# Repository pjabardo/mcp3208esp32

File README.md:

# mcp3208esp32
MCP3208 data acquisition with ESP32

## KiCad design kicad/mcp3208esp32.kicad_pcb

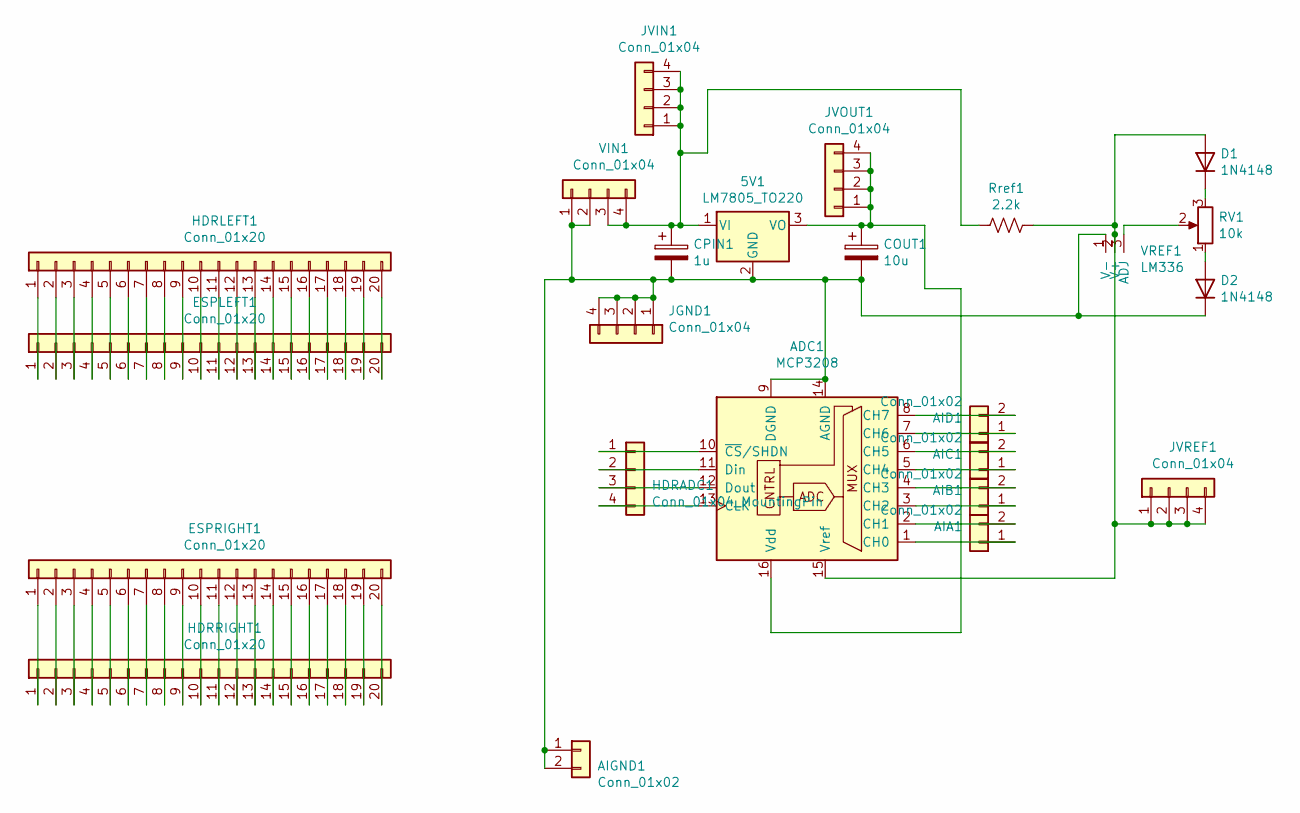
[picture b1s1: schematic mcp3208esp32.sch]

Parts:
5V1: LM7805_TO220; TO-220-3_Vertical
ADC1: MCP3208; DIP-16_W7.62mm
AIA1: Conn_01x02; TerminalBlock_bornier-2_P5.08mm
AIB1: Conn_01x02; TerminalBlock_bornier-2_P5.08mm
AIC1: Conn_01x02; TerminalBlock_bornier-2_P5.08mm
AID1: Conn_01x02; TerminalBlock_bornier-2_P5.08mm
AIGND1: Conn_01x02; TerminalBlock_bornier-2_P5.08mm
COUT1: 10u; CP_Radial_D5.0mm_P2.00mm
CPIN1: 1u; CP_Radial_D5.0mm_P2.00mm
D1, D2: 1N4148; D_DO-35_SOD27_P7.62mm_Horizontal
ESPLEFT1: Conn_01x20; PinSocket_1x20_P2.54mm_Vertical
ESPRIGHT1: Conn_01x20; PinSocket_1x20_P2.54mm_Vertical
HDRADC1: Conn_01x04_MountingPin; PinHeader_1x04_P2.54mm_Vertical
HDRLEFT1: Conn_01x20; PinHeader_1x20_P2.54mm_Vertical
HDRRIGHT1: Conn_01x20; PinHeader_1x20_P2.54mm_Vertical
JGND1: Conn_01x04; PinHeader_1x04_P2.54mm_Vertical
JVIN1: Conn_01x04; PinHeader_1x04_P2.54mm_Vertical
JVOUT1: Conn_01x04; PinHeader_1x04_P2.54mm_Vertical
JVREF1: Conn_01x04; PinHeader_1x04_P2.54mm_Vertical
RV1: 10k; Potentiometer_Bourns_3296W_Vertical
Rref1: 2.2k; R_Axial_DIN0207_L6.3mm_D2.5mm_P10.16mm_Horizontal
VIN1: Conn_01x04; TerminalBlock_bornier-4_P5.08mm
VREF1: LM336; TO-92L_Inline

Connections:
unnamed: 5V1.1 (VI), CPIN1.1, JVIN1.1, JVIN1.2, JVIN1.3, JVIN1.4, Rref1.2, VIN1.3, VIN1.4
unnamed: 5V1.2 (GND), ADC1.9 (DGND), ADC1.14 (AGND), AIGND1.1, AIGND1.2, COUT1.2, CPIN1.2, D2.1 (K), JGND1.1, JGND1.2, JGND1.3, JGND1.4, VIN1.1, VIN1.2, VREF1.1 (V-)
unnamed: 5V1.3 (VO), ADC1.16 (Vdd), COUT1.1, JVOUT1.1, JVOUT1.2, JVOUT1.3, JVOUT1.4
unnamed: ADC1.1 (CH0), AIA1.1
unnamed: ADC1.2 (CH1), AIA1.2
unnamed: ADC1.3 (CH2), AIB1.1
unnamed: ADC1.4 (CH3), AIB1.2
unnamed: ADC1.5 (CH4), AIC1.1
unnamed: ADC1.6 (CH5), AIC1.2
unnamed: ADC1.7 (CH6), AID1.1
unnamed: ADC1.8 (CH7), AID1.2
unnamed: ADC1.10 (~CS~/SHDN), HDRADC1.1
unnamed: ADC1.11 (Din), HDRADC1.2
unnamed: ADC1.12 (Dout), HDRADC1.3
unnamed: ADC1.13 (CLK), HDRADC1.4
unnamed: ADC1.15 (Vref), D1.2 (A), JVREF1.1, JVREF1.2, JVREF1.3, JVREF1.4, Rref1.1, VREF1.2 (V+)
unnamed: D1.1 (K), RV1.3
unnamed: D2.2 (A), RV1.1
unnamed: ESPLEFT1.1, HDRLEFT1.1
unnamed: ESPLEFT1.2, HDRLEFT1.2
unnamed: ESPLEFT1.3, HDRLEFT1.3
unnamed: ESPLEFT1.4, HDRLEFT1.4
unnamed: ESPLEFT1.5, HDRLEFT1.5
unnamed: ESPLEFT1.6, HDRLEFT1.6
unnamed: ESPLEFT1.7, HDRLEFT1.7
unnamed: ESPLEFT1.8, HDRLEFT1.8
unnamed: ESPLEFT1.9, HDRLEFT1.9
unnamed: ESPLEFT1.10, HDRLEFT1.10
unnamed: ESPLEFT1.11, HDRLEFT1.11
unnamed: ESPLEFT1.12, HDRLEFT1.12
unnamed: ESPLEFT1.13, HDRLEFT1.13
unnamed: ESPLEFT1.14, HDRLEFT1.14
unnamed: ESPLEFT1.15, HDRLEFT1.15
unnamed: ESPLEFT1.16, HDRLEFT1.16
unnamed: ESPLEFT1.17, HDRLEFT1.17
unnamed: ESPLEFT1.18, HDRLEFT1.18
unnamed: ESPLEFT1.19, HDRLEFT1.19
unnamed: ESPLEFT1.20, HDRLEFT1.20
unnamed: ESPRIGHT1.1, HDRRIGHT1.1
unnamed: ESPRIGHT1.2, HDRRIGHT1.2
unnamed: ESPRIGHT1.3, HDRRIGHT1.3
unnamed: ESPRIGHT1.4, HDRRIGHT1.4
unnamed: ESPRIGHT1.5, HDRRIGHT1.5
unnamed: ESPRIGHT1.6, HDRRIGHT1.6
unnamed: ESPRIGHT1.7, HDRRIGHT1.7
unnamed: ESPRIGHT1.8, HDRRIGHT1.8
unnamed: ESPRIGHT1.9, HDRRIGHT1.9
unnamed: ESPRIGHT1.10, HDRRIGHT1.10
unnamed: ESPRIGHT1.11, HDRRIGHT1.11
unnamed: ESPRIGHT1.12, HDRRIGHT1.12
unnamed: ESPRIGHT1.13, HDRRIGHT1.13
unnamed: ESPRIGHT1.14, HDRRIGHT1.14
unnamed: ESPRIGHT1.15, HDRRIGHT1.15
unnamed: ESPRIGHT1.16, HDRRIGHT1.16
unnamed: ESPRIGHT1.17, HDRRIGHT1.17
unnamed: ESPRIGHT1.18, HDRRIGHT1.18
unnamed: ESPRIGHT1.19, HDRRIGHT1.19
unnamed: ESPRIGHT1.20, HDRRIGHT1.20
unnamed: RV1.2, VREF1.3 (ADJ)

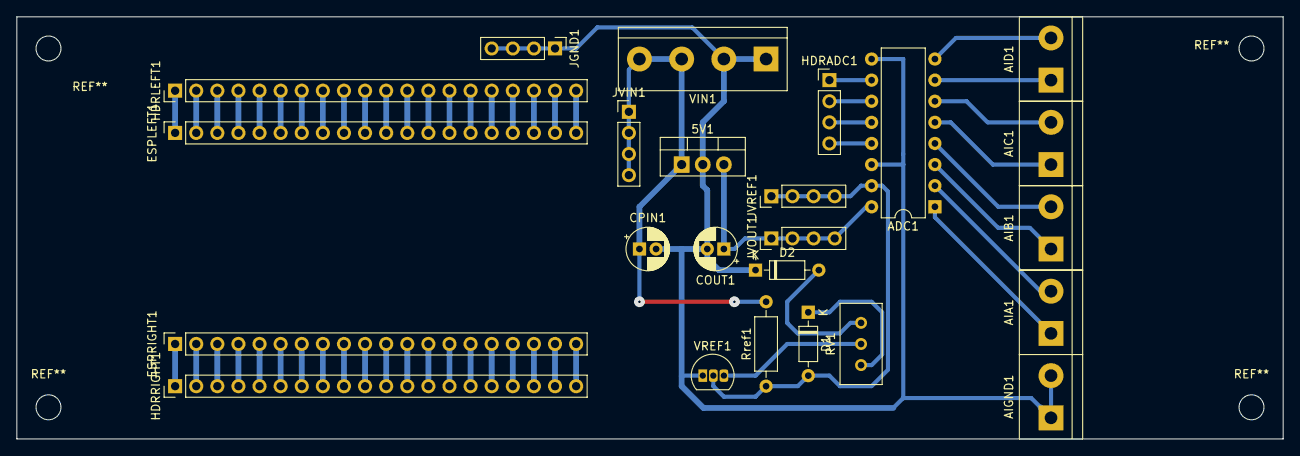
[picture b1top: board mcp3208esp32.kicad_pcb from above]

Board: 2 copper layers, 152.4 x 50.8 mm, 24 parts (0 on the bottom side), 59 nets.

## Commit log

2020-10-12 Initial commit of the mcp3208esp32 project.
    For now I am just adding the board.
2020-10-12 Modified the source of the voltage reference
    Now it uses the input voltage in contrast to before when the regulated 5V was the source for the reference voltage. This is an improvement because now the board can use 5V or 2.5V reference.
2020-10-14 Started working on the software
    For now I'm using the example on Mcp320x library. It is not working but I suspect that this is due to the use of the input buffers: If there is no input, the output from the op amp is unstable. A pos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
    This might not be the best solution. Perhaps a better op amp could be used. Since signal conditioning will be used, it might be interesting to eliminate the buffer entirely. It will be much simpler.
2020-10-16 Removed the operational amplifier
    It was not working and not helping. So for now I removed it.
    I also added a header connector that exposes the reference voltage to other applications.
2020-10-17 Updated the pcb without the op amps
    AGND and DGND are connected. Any signal conditioning will have to be done upstream.
2020-10-18 Built the board and tested it. It is working
    Now I need to write the software side of it.
